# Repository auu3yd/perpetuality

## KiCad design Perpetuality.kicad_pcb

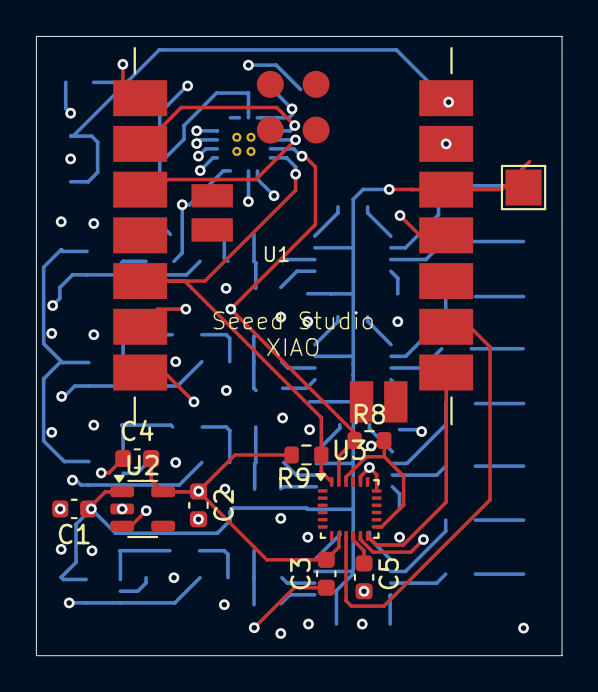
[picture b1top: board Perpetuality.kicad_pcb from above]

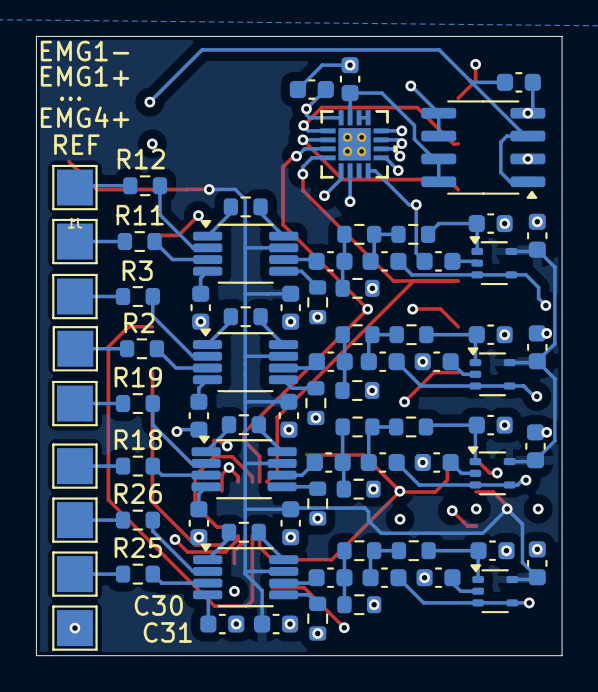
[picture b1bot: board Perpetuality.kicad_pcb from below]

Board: 6 copper layers, 29.2 x 34.4 mm, 89 parts (78 on the bottom side), 74 nets.

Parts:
...: Conn_01x01; TestPoint_Pad_2.0x2.0mm
C1, C2: 1uF; C_0603_1608Metric
C3, C4, C5, C6, C7, C13, C14, C17, C18, C21, C22, C23, C24, C28, C29, C30, C31, C35, C36: 0.1uF; C_0603_1608Metric
C8, C9, C10, C16, C25, C32: 1µF; C_0603_1608Metric
C11, C12, C19, C20, C26, C27, C33, C34: 33nF; C_0603_1608Metric
C15: 2.2µF; C_0603_1608Metric
EMG1+, EMG1-, EMG4+: Conn_01x01; TestPoint_Pad_2.0x2.0mm
J1: Conn_01x04; TestPoint_Pad_2.0x2.0mm
J4, J7, J9, J10: Conn_01x01; TestPoint_Pad_2.0x2.0mm
R1, R10, R17, R24: 470Ω; R_0603_1608Metric
R2, R3, R4, R11, R12, R13, R18, R19, R20, R25, R26, R27: 47kΩ; R_0603_1608Metric
R5, R14, R21, R28: 15.9kΩ; R_0603_1608Metric
R6, R7, R15, R16, R22, R23, R29, R30: 10kΩ; R_0603_1608Metric
R8, R9: 3kΩ; R_0603_1608Metric
REF: Conn_01x01; TestPoint_Pad_2.0x2.0mm
U1: XIAO-nRF52840-SMD; SeeedStudio nRf52840
U2: NCV8164CSN180T1G; TSOT-23-5
U3: ICM-20948; InvenSense_QFN-24_3x3mm_P0.4mm
U4, U6, U10, U12: INA333xxDGK; VSSOP-8_3x3mm_P0.65mm
U5, U9, U11, U13: OPA333xxDCK; SOT-353_SC-70-5
U7: ADS7924IRTER; RTE16_1P7X1P7
U8: MCP1501-33xSN; SOIC-8_3.9x4.9mm_P1.27mm

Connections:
1V8: C2.1, C3.1, C4.1, C9.1, R8.2, R9.2, U2.5 (OUT), U3.8 (VDDIO), U3.13 (VDD), U3.22 (~CS), U7.16 (DVDD)
3V3: C1.1, C7.1, C14.1, C18.1, C22.1, C24.1, C29.1, C31.1, C36.1, J1.1, U1.12 (3V3), U2.1 (IN), U4.7 (V+), U5.5 (V+), U6.7 (V+), U9.5 (V+), U10.7 (V+), U11.5 (V+), U12.7 (V+), U13.5 (V+)
5V: C15.1, U1.14 (5V), U8.1 (VDD), U8.3 (~SHDN)
*INT: U1.3 (P0.28_A2_D2), U7.2 (*INT)
*RESET: U1.2 (P0.03_A1_D1), U7.1 (*RESET)
/EMG1/Amplified_Signal: C16.1, U6.6
/EMG1/EMG_OUT: C20.2, U7.12 (CH0), U9.3 (-), U9.4
/EMG1/High-pass_Signal: C16.2, R14.2, R15.1
/EMG2/Amplified_Signal: C8.1, U4.6
/EMG2/EMG_OUT: C11.2, U5.3 (-), U5.4, U7.11 (CH1)
/EMG2/High-pass_Signal: C8.2, R5.2, R6.1
/EMG3/Amplified_Signal: C25.1, U10.6
/EMG3/EMG_OUT: C26.2, U7.10 (CH2), U11.3 (-), U11.4
/EMG3/High-pass_Signal: C25.2, R21.2, R22.1
/EMG4/Amplified_Signal: C32.1, U12.6
/EMG4/EMG_OUT: C33.2, U7.9 (CH3), U13.3 (-), U13.4
/EMG4/High-pass_Signal: C32.2, R28.2, R29.1
A0: U1.1 (P0.02_A0_D0), U7.5 (A0)
AD0: U1.9 (P1.13_D8_SCK), U3.9 (SDO/AD0)
E1+: EMG1+.1, R11.1
E1-: EMG1-.1, R12.1
E2+: EMG4+.1, R2.1
E2-: ....1, R3.1
E3+: J7.1, R18.1
E3-: R19.1, REF.1
E4+: J9.1, R25.1
E4-: J10.1, R26.1
EN: U1.11 (P1.15_D10_MOSI), U2.3 (EN)
FSYNC: U1.7 (P1.11_D6_TX), U3.11 (FSYNC)
GND: C6.2, C7.2, C12.1, C13.2, C14.2, C17.2, C18.2, C19.1, C21.2, C22.2, C23.2, C24.2, C27.1, C28.2, C29.2, C30.2, C31.2, C34.1, C35.2, C36.2, R5.1, R14.1, R21.1, R28.1, U7.8 (AGND)
GNDD: C1.2, C2.2, C3.2, C4.2, C5.2, C9.2, C10.2, C15.2, U1.13 (GND), U2.2 (GND), U3.18 (GND), U3.20 (GND), U7.6 (DGND), U8.2 (GND), U8.4 (GND), U8.5 (GND), U8.6 (GND)
INT1: U1.8 (P1.12_D7_RX), U3.12 (INT1)
unnamed: C11.1, R6.2, R7.1
unnamed: C20.1, R15.2, R16.1
unnamed: C26.1, R22.2, R23.1
unnamed: C33.1, R29.2, R30.1
unnamed: R1.1, U4.8 (Rg)
unnamed: R1.2, U4.1 (Rg)
unnamed: R10.1, U6.8 (Rg)
unnamed: R10.2, U6.1 (Rg)
unnamed: R17.1, U10.8 (Rg)
unnamed: R17.2, U10.1 (Rg)
unnamed: R24.1, U12.8 (Rg)
unnamed: R24.2, U12.1 (Rg)
unnamed: C5.1, U3.10 (REGOUT)
unnamed: R2.2, U4.3 (+)
unnamed: R3.2, U4.2 (-)
unnamed: R4.2, U4.5 (Ref)
unnamed: C6.1, U4.4 (V-)
unnamed: C12.2, R7.2, U5.1 (+)
unnamed: C13.1, U5.2 (V-)
unnamed: R11.2, U6.3 (+)
unnamed: R12.2, U6.2 (-)
unnamed: R13.2, U6.5 (Ref)
unnamed: C17.1, U6.4 (V-)
unnamed: U7.13 (MUXOUT), U7.14 (ADCIN)
unnamed: C19.2, R16.2, U9.1 (+)
unnamed: C21.1, U9.2 (V-)
unnamed: R18.2, U10.3 (+)
unnamed: R19.2, U10.2 (-)
unnamed: R20.2, U10.5 (Ref)
unnamed: C23.1, U10.4 (V-)
unnamed: C27.2, R23.2, U11.1 (+)
unnamed: C28.1, U11.2 (V-)
unnamed: R25.2, U12.3 (+)
unnamed: R26.2, U12.2 (-)
unnamed: R27.2, U12.5 (Ref)
unnamed: C30.1, U12.4 (V-)
unnamed: C34.2, R30.2, U13.1 (+)
unnamed: C35.1, U13.2 (V-)
REF: J4.1, R4.1, R13.1, R20.1, R27.1
SCL: R8.1, U1.6 (P0.05_A5_D5_SCL), U3.23 (SCL/SCLK), U7.3 (SCLK)
SDA: R9.1, U1.5 (P0.04_A4_D4_SDA), U3.24 (SDA/SDI), U7.4 (SDA)
VREF: C10.1, U7.15 (AVDD), U8.7 (OUT), U8.8 (FB)

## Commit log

2025-10-12 OG Schematic Redesign
    Implemented a cheaper, more-suitable ADS7924IRTER (with a dedicated MCP1501T-33E/SN "series" voltage reference) to allow for 4x EMG sensor circuits. Added appropriate decoupling capacitors and fixed 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
2025-11-15 newest version sent to jlc
